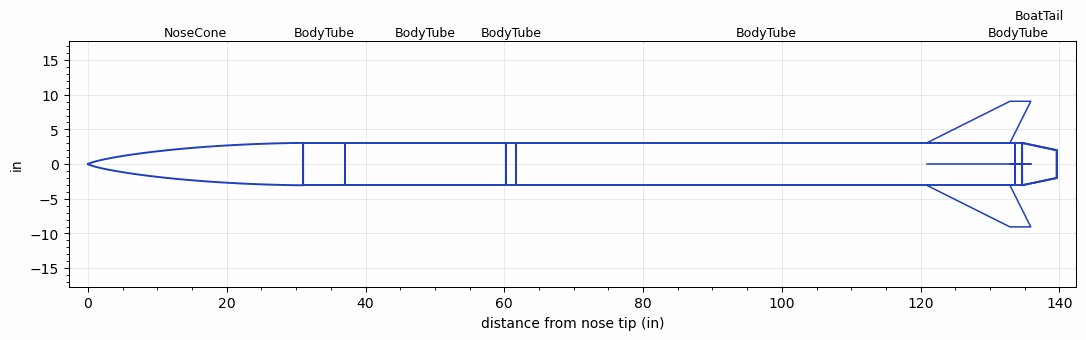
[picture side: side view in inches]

<RASAeroDocument>
 <FileVersion>2</FileVersion>
 <RocketDesign>
  <NoseCone>
   <Length>31</Length>
   <Diameter>6.1</Diameter>
   <Shape>LV-Haack</Shape>
   <BluntRadius>0.03</BluntRadius>
   <Location>0</Location>
  </NoseCone>
  <BodyTube>
   <Length>6</Length>
   <Diameter>6.1</Diameter>
   <Location>31</Location>
  </BodyTube>
  <BodyTube>
   <Length>23.25</Length>
   <Diameter>6.1</Diameter>
   <Location>37</Location>
  </BodyTube>
  <BodyTube>
   <Length>1.5</Length>
   <Diameter>6.1</Diameter>
   <Location>60.25</Location>
  </BodyTube>
  <BodyTube>
   <Length>71.875</Length>
   <Diameter>6.1</Diameter>
   <LaunchLugDiameter>0.214</LaunchLugDiameter>
   <LaunchLugLength>0.214</LaunchLugLength>
   <Location>61.75</Location>
   <Fin>
    <Count>4</Count>
    <Chord>12</Chord>
    <Span>6</Span>
    <SweepDistance>12</SweepDistance>
    <TipChord>3</TipChord>
    <Thickness>0.266</Thickness>
    <LERadius>0.022</LERadius>
    <Location>12.75</Location>
    <AirfoilSection>Double Wedge</AirfoilSection>
    <FX1>3.75</FX1>
   </Fin>
  </BodyTube>
  <BodyTube>
   <Length>1</Length>
   <Diameter>6.1</Diameter>
   <Location>133.625</Location>
   <BoattailLength>5</BoattailLength>
   <BoattailRearDiameter>4</BoattailRearDiameter>
  </BodyTube>
  <BoatTail>
   <Length>5</Length>
   <Diameter>6.1</Diameter>
   <RearDiameter>4</RearDiameter>
   <Location>134.625</Location>
  </BoatTail>
  <Surface>Smooth Paint</Surface>
  <ModifiedBarrowman>False</ModifiedBarrowman>
  <Turbulence>False</Turbulence>
  <UseBooster1>False</UseBooster1>
  <UseBooster2>False</UseBooster2>
 </RocketDesign>
 <LaunchSite>
  <Altitude>1368</Altitude>
  <Pressure>28.92</Pressure>
  <RodAngle>2.5</RodAngle>
  <RodLength>12.5</RodLength>
  <Temperature>85</Temperature>
  <WindSpeed>24</WindSpeed>
 </LaunchSite>
 <Recovery>
  <Altitude1>1000</Altitude1>
  <Altitude2>1000</Altitude2>
  <DeviceType1>None</DeviceType1>
  <DeviceType2>None</DeviceType2>
  <Event1>False</Event1>
  <Event2>False</Event2>
  <Size1>1</Size1>
  <Size2>1</Size2>
  <EventType1>None</EventType1>
  <EventType2>None</EventType2>
  <CD1>1.33</CD1>
  <CD2>1.33</CD2>
 </Recovery>
 <SimulationList>
  <Simulation>
   <SustainerEngine>O5500X  (AT)</SustainerEngine>
   <SustainerLaunchWt>74.1</SustainerLaunchWt>
   <SustainerNozzleDiameter>3.6</SustainerNozzleDiameter>
   <SustainerCG>89.16</SustainerCG>
   <SustainerIgnitionDelay>0</SustainerIgnitionDelay>
   <Booster1SeparationDelay>0</Booster1SeparationDelay>
   <Booster1IgnitionDelay>0</Booster1IgnitionDelay>
   <IncludeBooster1>False</IncludeBooster1>
   <Booster2Delay>0</Booster2Delay>
   <IncludeBooster2>False</IncludeBooster2>
   <TimetoApogee>39.46938</TimetoApogee>
   <MaxAltitude>30296.49</MaxAltitude>
   <MaxVelocity>2095.744</MaxVelocity>
  </Simulation>
 </SimulationList>
</RASAeroDocument>
